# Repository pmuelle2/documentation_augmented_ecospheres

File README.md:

# Augmented Ecospheres
 technical documentations

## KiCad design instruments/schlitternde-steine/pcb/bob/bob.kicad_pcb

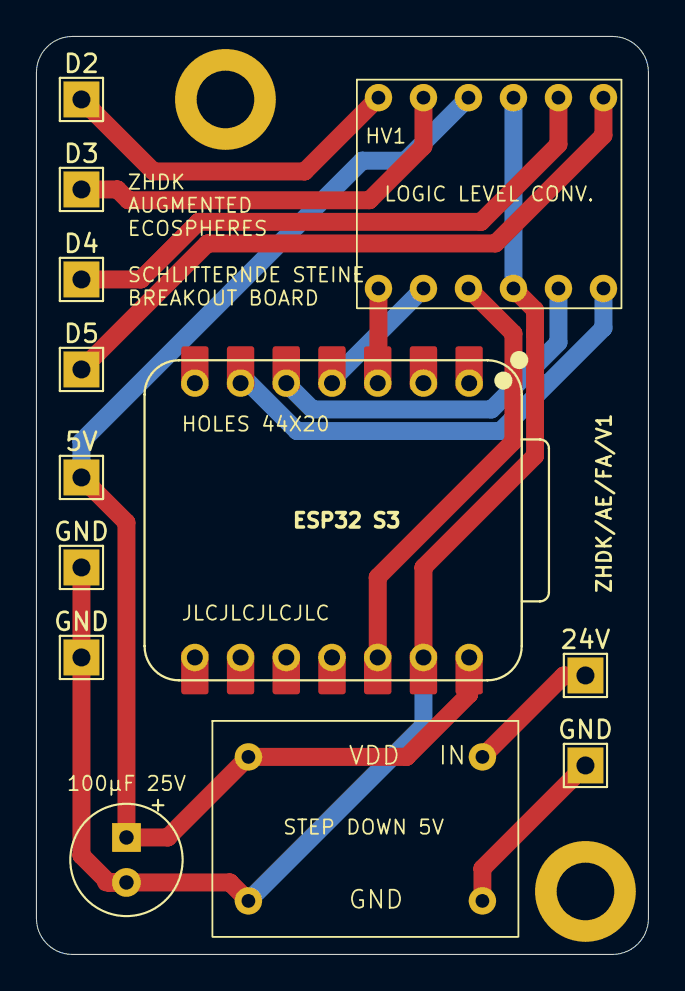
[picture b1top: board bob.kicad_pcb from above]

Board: 2 copper layers, 34.0 x 51.0 mm, 13 parts (0 on the bottom side), 13 nets.

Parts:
5V, 24V: TestPoint; TestPoint_THTPad_2.0x2.0mm_Drill1.0mm
100µF 25V: C_Polarized; CP_Radial_Tantal_D6.0mm_P2.50mm
D2, D3, D4, D5: TestPoint; TestPoint_THTPad_2.0x2.0mm_Drill1.0mm
ESP32 S3: XIAO-ESP32-S3-DIP; XIAO-ESP32S3-DIP
GND: TestPoint; TestPoint_THTPad_2.0x2.0mm_Drill1.0mm
GND#2, GND#3: TestPoint; TestPoint_THTPad_2.0x2.0mm_Drill1.0mm
LOGIC LEVEL CONV.: LogicLevelShifter
STEP DOWN 5V: StepDown5V

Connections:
+24V: 24V.1, STEP DOWN 5V.1 (24V)
GND 5V: 100µF 25V.2, ESP32 S3.13 (GND), GND#2.1, GND#3.1, LOGIC LEVEL CONV..4 (GND), LOGIC LEVEL CONV..10 (GND), STEP DOWN 5V.4 (GND)
GND 24V: GND.1, STEP DOWN 5V.2 (GND)
unnamed: ESP32 S3.3 (GPIO3/D2/A2), LOGIC LEVEL CONV..7 (LV1)
unnamed: ESP32 S3.4 (GPIO4/D3/A3), LOGIC LEVEL CONV..8 (LV2)
unnamed: ESP32 S3.5 (GPIO5/D4/I2C_SDA), LOGIC LEVEL CONV..11 (LV3)
unnamed: ESP32 S3.6 (GPIO9/D5/I2C_SCL), LOGIC LEVEL CONV..12 (LV4)
unnamed: ESP32 S3.12 (VCC_3V3), LOGIC LEVEL CONV..9 (LV)
unnamed: D2.1, LOGIC LEVEL CONV..1 (HV1)
unnamed: D3.1, LOGIC LEVEL CONV..2 (HV2)
unnamed: D4.1, LOGIC LEVEL CONV..5 (HV3)
unnamed: D5.1, LOGIC LEVEL CONV..6 (HV4)
VDD 5V: 5V.1, 100µF 25V.1, ESP32 S3.14 (VBUS), LOGIC LEVEL CONV..3 (HV), STEP DOWN 5V.3 (5V)

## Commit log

2025-04-24 Rename readthedocs.yml to .readthedocs.yml
2025-04-24 Rename .readthedocs.yml to .readthedocs.yaml
2025-04-24 Rename .readthedocs.yaml to .readthedocs.yml
2025-04-24 Adding a download-folder
2025-04-27 audio-box doc added
2025-10-28 prototype files of schlitternde-steine instrument
    files for building a prototype instrument to simulate a constant sliding of stones. inspired by the constant rockfall and rocksliding in the contemporary alps
2025-10-28 back of cad model v1
    add cad model v1 of schlitternde steine mechanics
2025-11-07 change diameter of internal bevelgear connector
    added .9mm to diameter internal surface that connects to the bearing. the shrinking with abs+ was too much and the connection too loose.
2025-11-15 initial release controlbox / update schlitternde steine bevelgear connector
2025-11-25 finetuneing 3d files
    enlarge top bevelgear for abs shrinking, add bearing clamp to top of the connector.
2025-11-25 software based on esp stepper server
2025-11-25 add screenshot of assembly
2026-02-03 move dev. stl to archive
2026-02-03 create controller pcb breakoutboard v1
2026-02-03 add pre-production version of stl
    to be printed in ASA+ 4 Walls, 40% infill, infill/wall overlap 50%, bottom & top 5 layers
2026-02-03 Update AE_schlitternde-steine_foot_4x.stl
    add m4 lug screw hole, ist aber wohl noch zu tief am boden.
2026-02-04 update print tolerances, add cable management to controlbox
2026-02-04 update bearing tolerances
2026-02-06 last update controlbox
2026-02-06 add gcode file
2026-02-12 update motor config
2026-03-17 UPDATE FEET 3d models
2026-04-29 Added Max Patch / Chataigne
    backup max patch and chataigne timeline of current state, 29. april 2026, 11h00
2026-04-29 housekeeping
    moving controller out of schlitternde steine instrument, as it is instrument agnostic and more instruments are planned
2026-04-29 housekeeping 2
2026-04-29 added image
2026-04-30 backup installation patches
2026-05-01 backup patch helferei
2026-05-04 backup final composition im griess helferei
2026-05-06 add static website
